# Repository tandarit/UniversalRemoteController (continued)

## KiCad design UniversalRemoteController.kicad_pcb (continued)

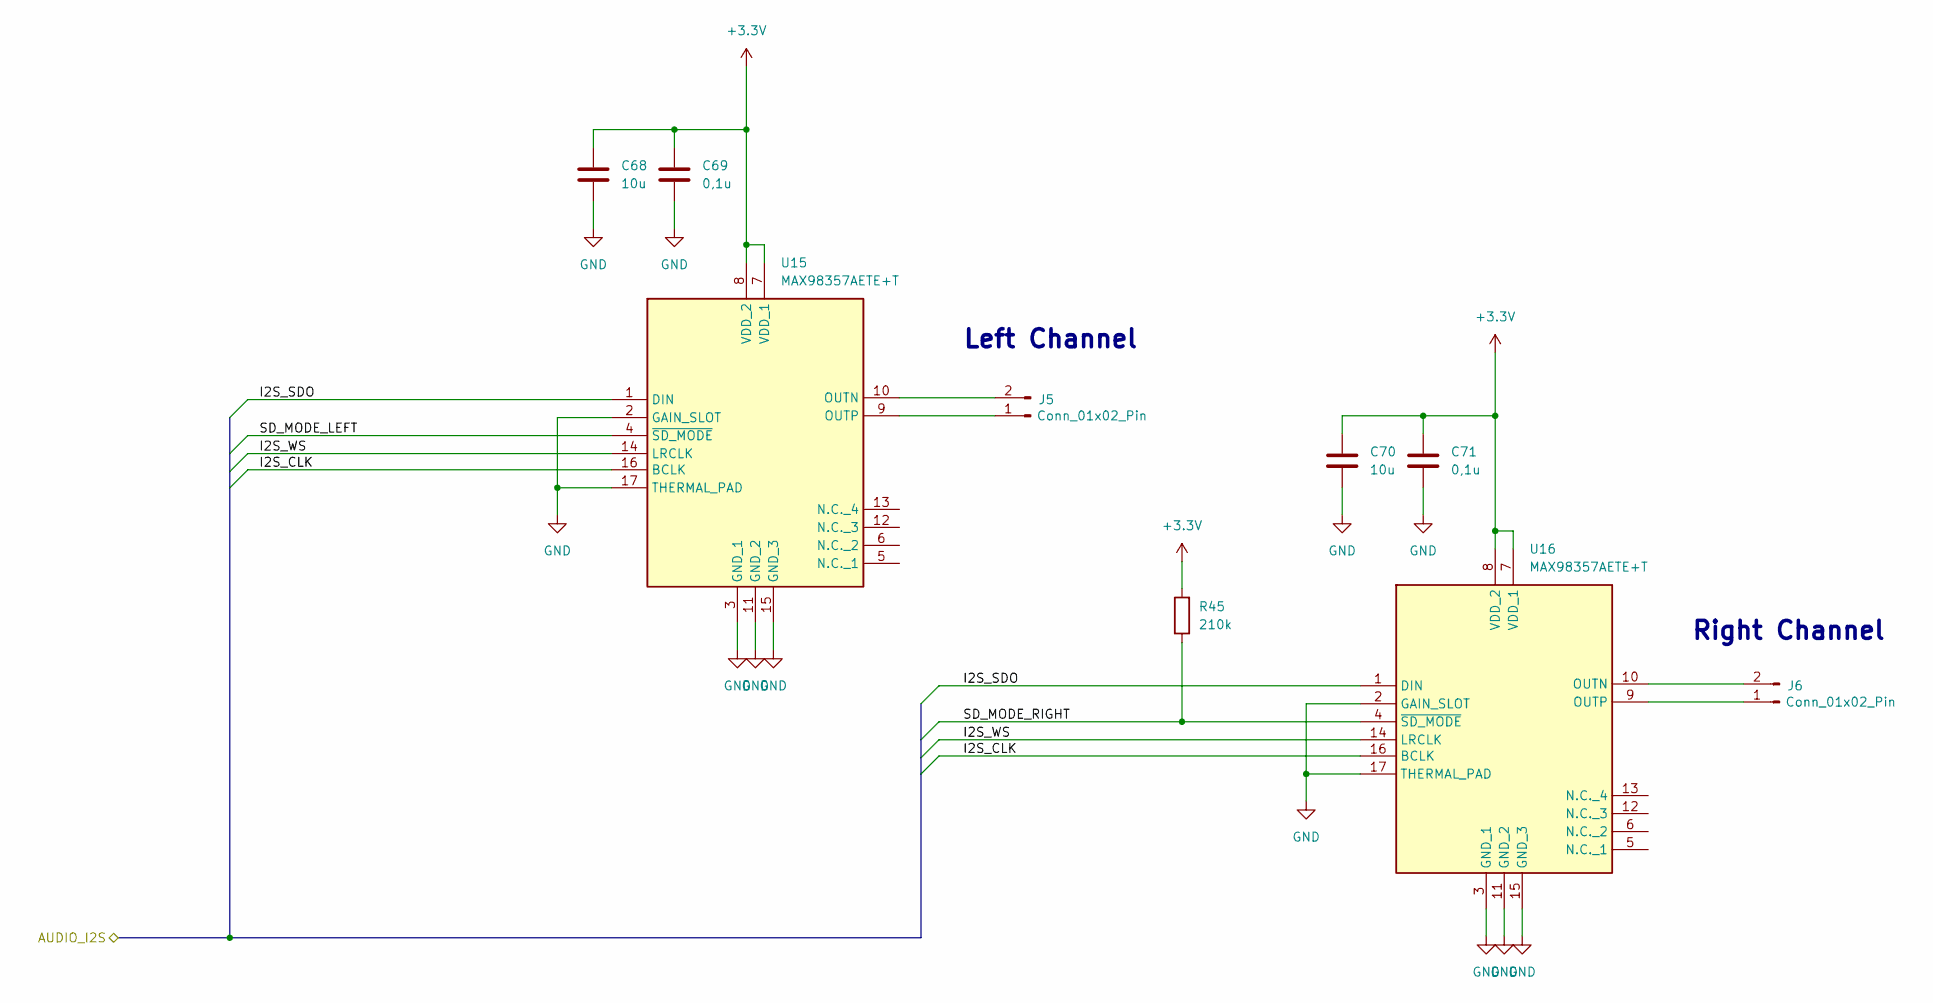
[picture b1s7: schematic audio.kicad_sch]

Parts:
C68, C70: 10u; C_0805_2012Metric
C69, C71: 0,1u; C_0603_1608Metric
J5, J6: Conn_01x02_Pin; PinHeader_1x02_P2.54mm_Horizontal
R45: 210k; R_0402_1005Metric
U15, U16: MAX98357AETE+T; QFN50P300X300X80-17N; Mouser Part Number 700-MAX98357AETE+T

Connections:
+3.3V: C68.1, C69.1, C70.1, C71.1, R45.2, U15.7 (VDD_1), U15.8 (VDD_2), U16.7 (VDD_1), U16.8 (VDD_2); also elsewhere on the board
/Audio/I2S_CLK: U15.16 (BCLK), U16.16 (BCLK)
/Audio/I2S_SDO: U15.1 (DIN), U16.1 (DIN)
/Audio/I2S_WS: U15.14 (LRCLK), U16.14 (LRCLK)
/Audio/SD_MODE_LEFT: U15.4 (~SD_MODE)
/Audio/SD_MODE_RIGHT: R45.1, U16.4 (~SD_MODE)
GND: C68.2, C69.2, C70.2, C71.2, U15.2 (GAIN_SLOT), U15.3 (GND_1), U15.11 (GND_2), U15.15 (GND_3), U15.17 (THERMAL_PAD), U16.2 (GAIN_SLOT), U16.3 (GND_1), U16.11 (GND_2), U16.15 (GND_3), U16.17 (THERMAL_PAD); also elsewhere on the board
unnamed: J5.1, U15.9 (OUTP)
unnamed: J5.2, U15.10 (OUTN)
unnamed: J6.1, U16.9 (OUTP)
unnamed: J6.2, U16.10 (OUTN)

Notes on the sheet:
Left Channel
Right Channel

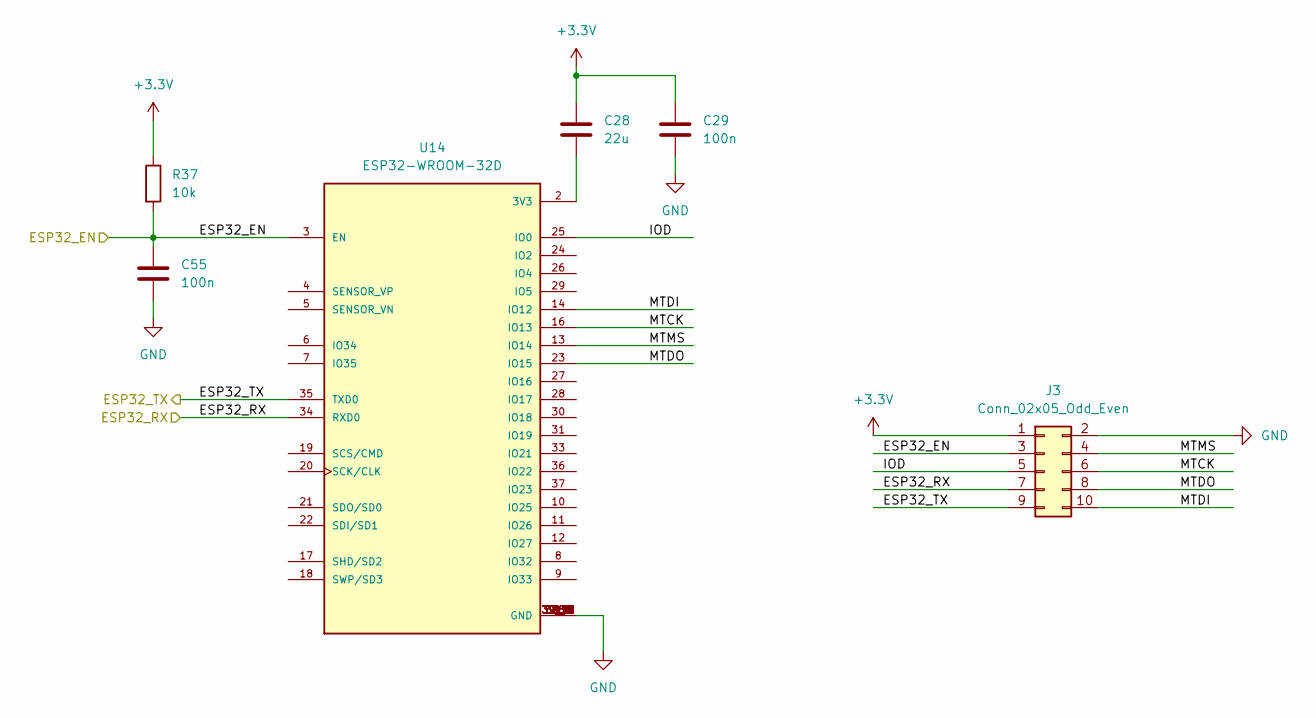
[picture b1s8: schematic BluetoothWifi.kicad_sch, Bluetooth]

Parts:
C28: 22u; C_0805_2012Metric
C29, C55: 100n; C_0402_1005Metric
J3: Conn_02x05_Odd_Even; PinHeader_2x05_P1.27mm_Vertical_SMD
R37: 10k; R_0402_1005Metric
U14: ESP32-WROOM-32D; MODULE_ESP32-WROOM-32D; PARTREV 1.9

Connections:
+3.3V: C28.1, C29.1, J3.1, R37.1; also elsewhere on the board
/BluetoothWiFi/ESP32_EN: C55.1, J3.3, R37.2, U14.3 (EN); also elsewhere on the board
/BluetoothWiFi/ESP32_RX: J3.7, U14.34 (RXD0); also elsewhere on the board
/BluetoothWiFi/ESP32_TX: J3.9, U14.35 (TXD0); also elsewhere on the board
/BluetoothWiFi/IOD: J3.5, U14.25 (IO0)
/BluetoothWiFi/MTCK: J3.6, U14.16 (IO13)
/BluetoothWiFi/MTDI: J3.10, U14.14 (IO12)
/BluetoothWiFi/MTDO: J3.8, U14.23 (IO15)
/BluetoothWiFi/MTMS: J3.4, U14.13 (IO14)
GND: C29.2, C55.2, J3.2, U14.1 (GND), U14.15 (GND), U14.38 (GND), U14.39_1 (GND), U14.39_2 (GND), U14.39_3 (GND), U14.39_4 (GND), U14.39_5 (GND), U14.39_6 (GND), U14.39_7 (GND), U14.39_8 (GND), U14.39_9 (GND), U14.39_10 (GND), U14.39_11 (GND), U14.39_12 (GND), U14.39_13 (GND), U14.39_14 (GND), U14.39_15 (GND), U14.39_16 (GND), U14.39_17 (GND), U14.39_18 (GND), U14.39_19 (GND), U14.39_20 (GND), U14.39_21 (GND); also elsewhere on the board
unnamed: C28.2, U14.2 (3V3)

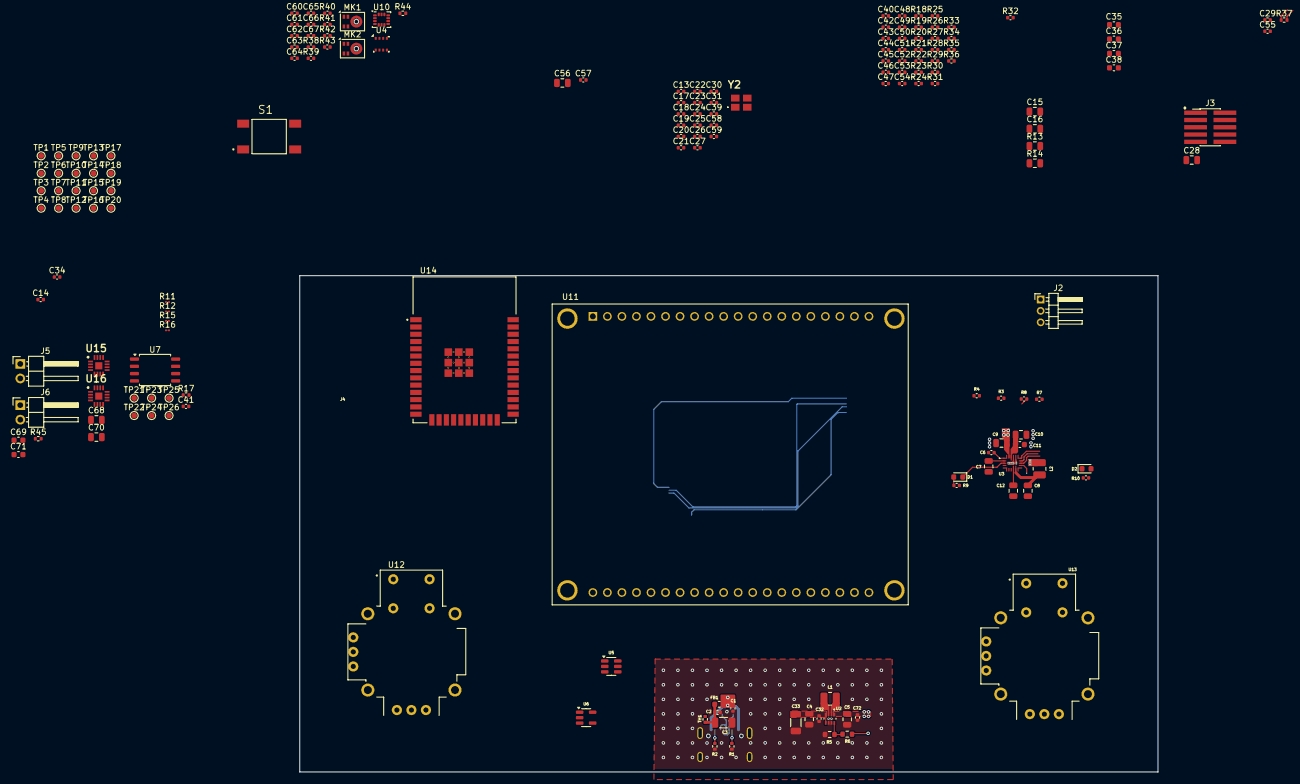
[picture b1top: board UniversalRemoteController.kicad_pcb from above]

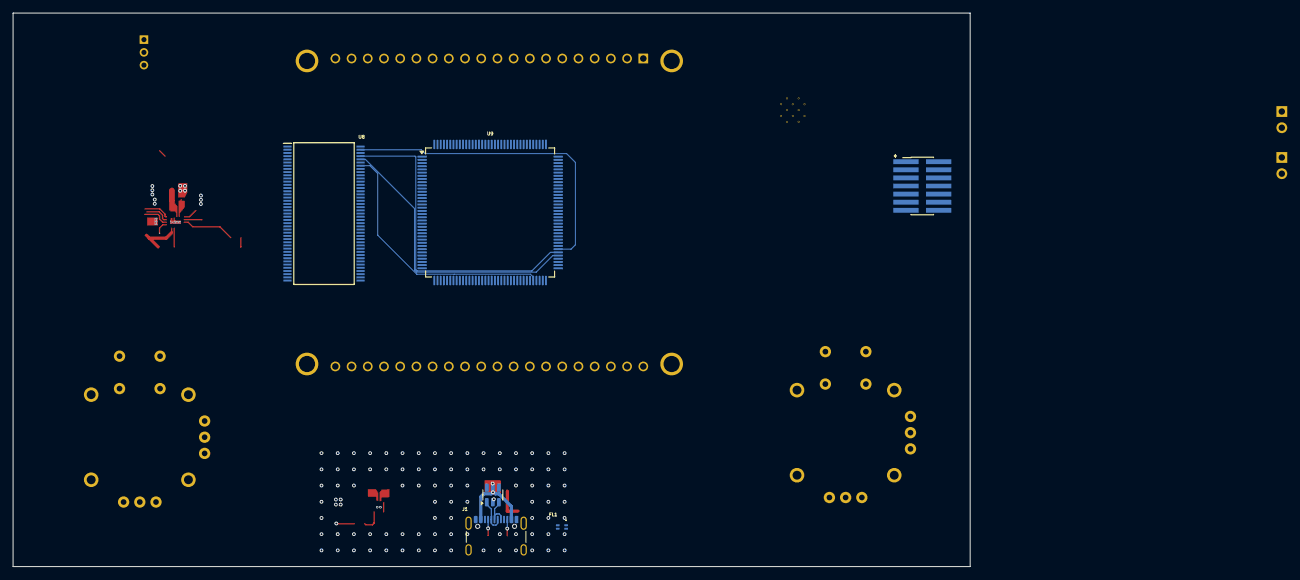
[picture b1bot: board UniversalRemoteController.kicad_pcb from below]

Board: 6 copper layers, 150.0 x 86.7 mm, 176 parts (6 on the bottom side), 155 nets.

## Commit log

2024-06-07 Add the SDRAM ic
    16MB SDRAM add
2024-06-23 Add the nrf and joystic module
2024-08-02 commit a sound version
2024-11-22 started the layout
